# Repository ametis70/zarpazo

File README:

# Zarpazo 

El club Bolsa de Gatos es el escenario de la final de un torneo de boxeo clandestino.Todo se vuelve aún más violento cuando la mafia irrumpe y lo sabotea.
¡Elegí a tu luchador y recuperá el trofeo en Zarpazo!

### Sobre el proyecto

Este es un videojuego que se realizó utilizando [Processing](https://processing.org/) y [Arduino](https://arduino.cc) para la décima muestra de fin de año de Taller de Diseño Multimedial 1 de la [Universidad Nacional de La Plata](www.unlp.edu.ar).

La temática de los videojuegos de este año fueron probervios, y él que fue asignado a nuestro grupo fue "Es una bolsa de gatos" 

Parte de la consigna era que los videojuegos debían tener una interacción no convencional, que se resolvió utilizando microswitches que eran presionados por bolsas que el jugador debe golpear.

Acá se puede ver un vídeo del juego en acción: [link a YouTube](https://www.youtube.com/watch?v=CN1-HlIt3Nw).

### El Staff ([Versión en wallpaper](http://i.imgur.com/HdKqGTs.png))

* Diseño
	* Álvaro Tomás Perez Dominguez
	* Julián Ramos
	* Manuel Alcolea

* Arte
	* Gastón Rodríguez
	* Leonel Rodríguez
	* Pilar Vales

* Arquigrafía
	* Camila Navarro
	* Feliciano Aguiar
	* Matias Arias

* Programación
	* Ian Mancini
	* Santiago Reartes

### Consideraciones finales 

En caso de que se descargue el código fuente del juego, hay que descargar primero la librería Minim desde el IDE de Processing para poder compilarlo([ver imágen](http://i.imgur.com/saRb8e3.png)).

Los controles para jugar con el teclado son la A para el azul, la S para el verde y la D para el rojo.

El juego está diseñado para que solo funcione en una resolución de 1366x768. En caso de que se modficara esto, habría que cambiar muchas posisciones y tamaños absolutos.

En el PCB(o el esquemático) de KiCad, los pines del conector que van a tierra y 5V están mal conectados, por lo que hay que cambiarlos antes de imprimir una placa.

Por cuestiones de tiempo y falta de conocimientos cuando se lanzó el trabajo práctico, gran parte del código del juego está desorganizado y desopotimizado, y hay varios bugs que quedaron sin resolver, pero ahora que la muestra ya pasó, todo eso probablemente quede así.

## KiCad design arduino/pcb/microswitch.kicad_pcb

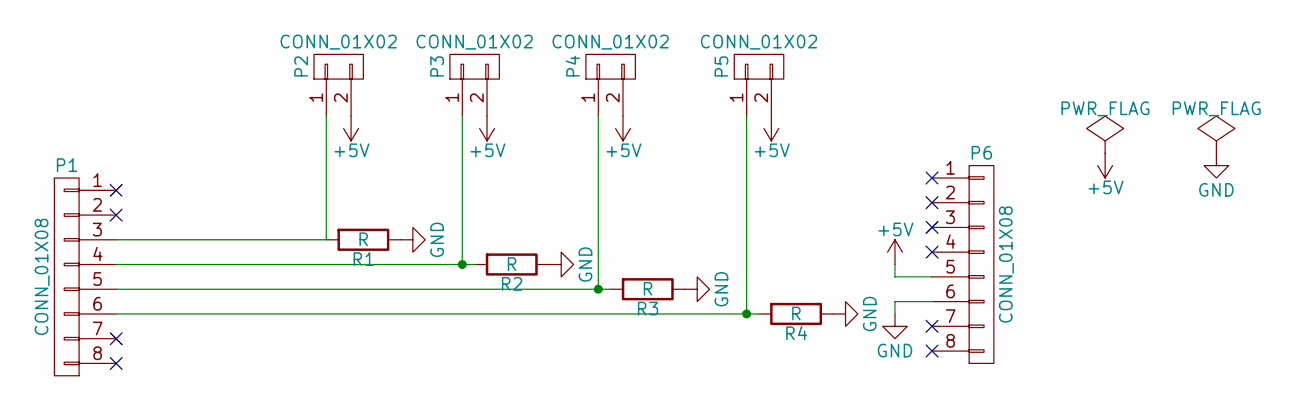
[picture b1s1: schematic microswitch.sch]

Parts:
P1, P6: CONN_01X08; Pin_Header_Straight_1x08
P2, P3, P4, P5: CONN_01X02; mkds_1,5-2
R1, R2, R3, R4: R; Resistor_Horizontal_RM10mm

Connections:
+5V: P2.2, P3.2, P4.2, P5.2, P6.5
GND: P6.6, R1.1, R2.1, R3.1, R4.1
unnamed: P1.3, P2.1, R1.2
unnamed: P1.4, P3.1, R2.2
unnamed: P1.5, P4.1, R3.2
unnamed: P1.6, P5.1, R4.2

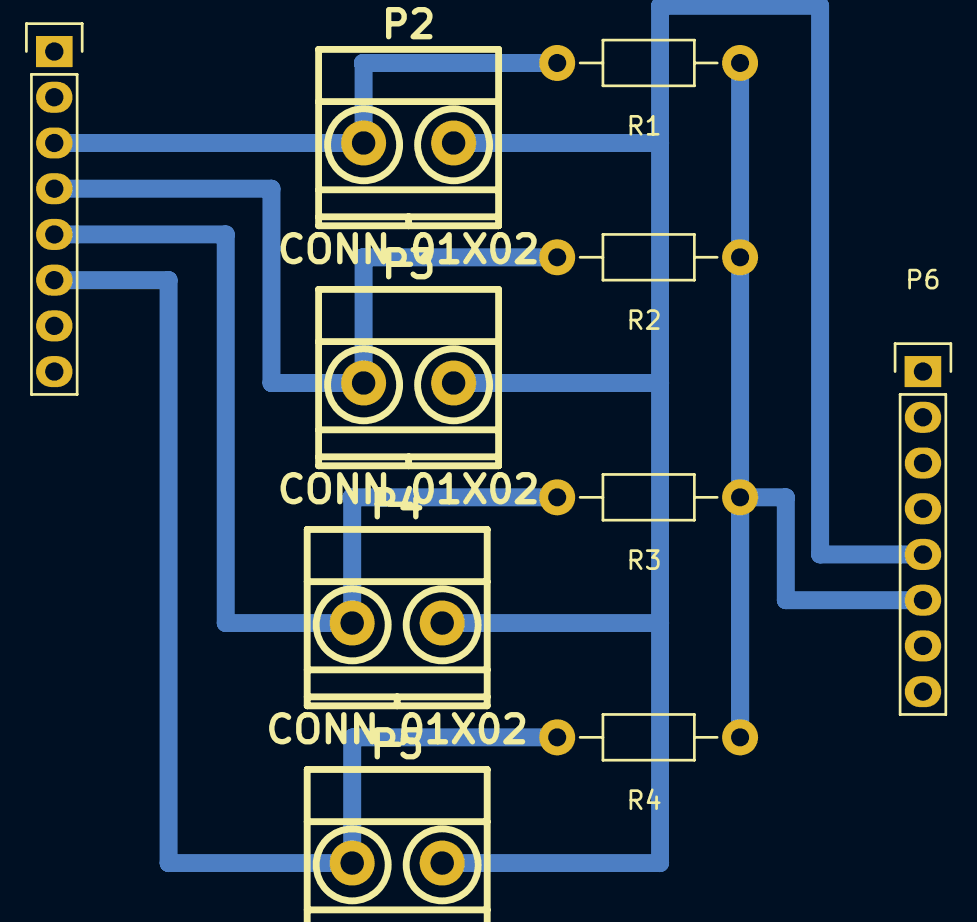
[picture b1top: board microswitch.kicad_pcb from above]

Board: 2 copper layers, 10 parts (0 on the bottom side), 6 nets.

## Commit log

2016-11-01 Add some placeholders and rework battle system
2016-11-05 Change file names
2016-11-05 Create level class and move variables
2016-11-06 Move certain methods and fields to new classes
2016-11-06 Further organization of classes
2016-11-09 Build general layout of levels' structure
2016-11-10 Add Manu's lifebar code, also cutscene's
2016-11-12 Add new class Juego and move a lot of stuff. Add Arduino code
2016-11-12 Add Windows files to .gitignore
2016-11-13 Add counter for battle
2016-11-13 Remove Arduino folder
2016-11-14 Add leaderboard and character select screen. Rework battle system
2016-11-15 Some changes
2016-11-16 Add classes for easing and fade, music library and animations(sort of)*
2016-11-21 Improve background and menus
2016-11-21 Add arduino files
2016-11-23 Add particles and feedback, modify character select screen and reduce number of battle system balls
2016-11-26 Organize some elements
2016-11-26 Add Ui class and separate Menu class into many classes
2016-11-28 Minor changes
2016-11-29 Add screen shake on hit and crosshair(bugged)
2016-11-30 Fix bug in crosshair and replace character icons and other minor stuff
2016-12-01 Add boxing gloves sprites and function. Stars now have color based on the bag that was hit
2016-12-02 Add noise-movement to boxing gloves
2016-12-02 Add damage indicator on damage recived
2016-12-04 Added function for KO
2016-12-04 Correct mistakes in KO-function
2016-12-05 Finish general structure of game
2016-12-05 Create general structure of game
2016-12-05 Replace the characters in selection-screen with new sprites
2016-12-06 Rework enemy animations code. Add dialogs in cutscenes. Finish first custscene and stage
2016-12-07 Add placeholders for the rest of the game
2016-12-08 Add final cutscenes and fix minor bugs
2016-12-09 Replace the dialogs from enemy characters with new ones
2016-12-09 Reinstitute music and fx and add a rudimentary score system
2016-12-09 Update leaderboard.csv
    leaderboard test
2016-12-09 Finish game
2016-12-10 Add readme, sound effects. Change music and some other minor stuff
2016-12-10 Rename README to README.md
2016-12-13 Modify Readme and fix some minor bugs
2016-12-13 Remove c5p library
2016-12-13 Modify README.md
2016-12-15 Correct typo
2020-03-30 Fix paths
